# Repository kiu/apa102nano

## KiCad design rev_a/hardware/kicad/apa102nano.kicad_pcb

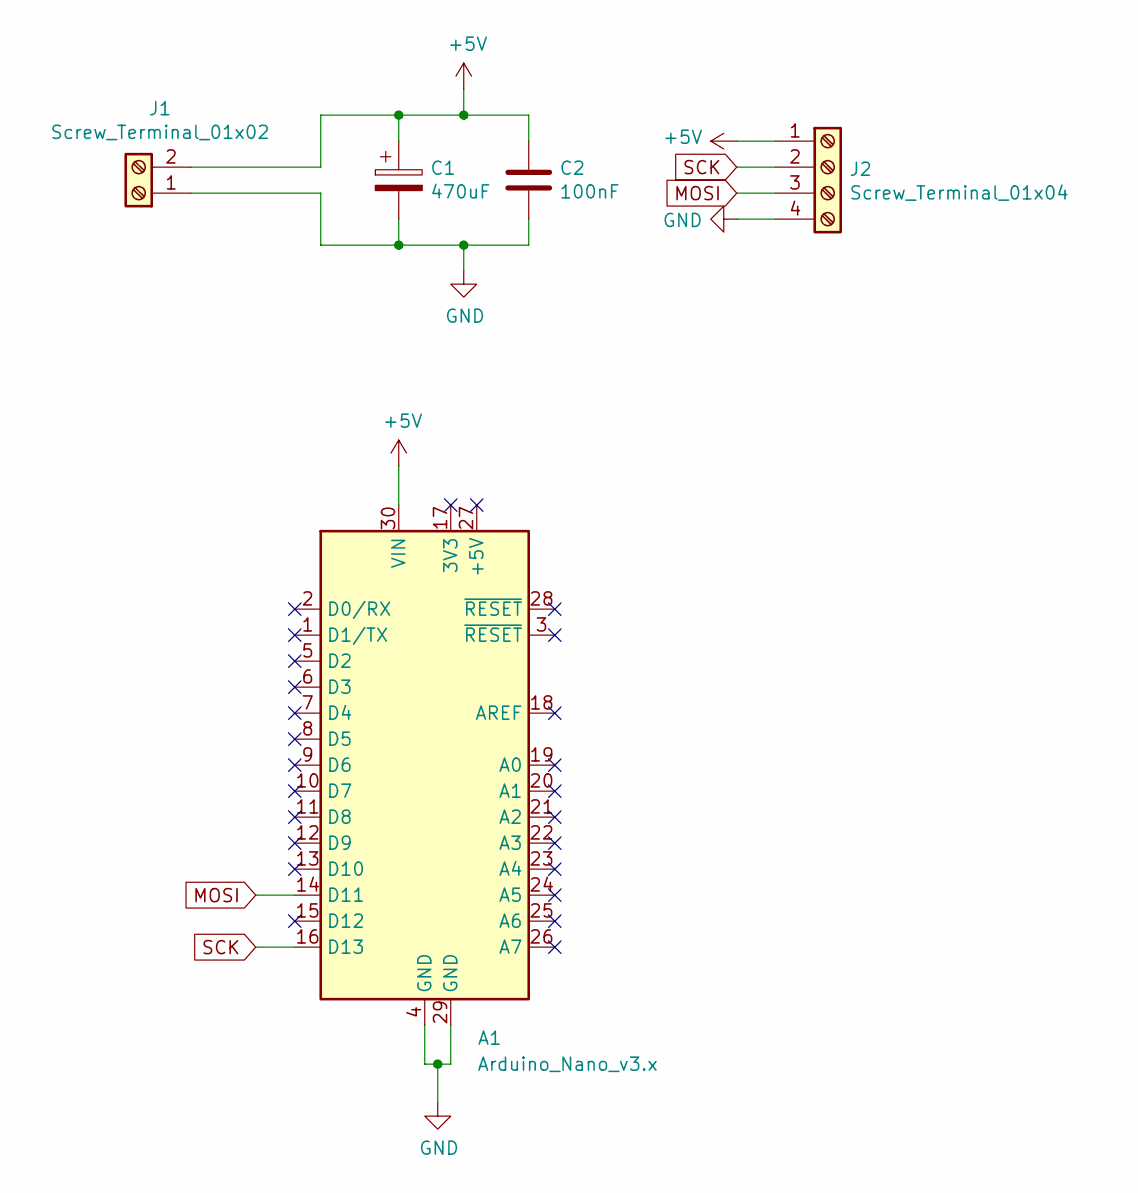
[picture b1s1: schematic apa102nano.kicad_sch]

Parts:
A1: Arduino_Nano_v3.x; Arduino_Nano
C1: 470uF; CP_Tantalum_Case-D_EIA-7343-31_Hand
C2: 100nF; C_0805_HandSoldering
J1: Screw_Terminal_01x02; TerminalBlock_bornier-2_P5.08mm
J2: Screw_Terminal_01x04; TerminalBlock_bornier-4_P5.08mm

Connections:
+5V: A1.30 (VIN), C1.1, C2.1, J1.2, J2.1
GND: A1.4 (GND), A1.29 (GND), C1.2, C2.2, J1.1, J2.4
MOSI: A1.14 (D11), J2.3
SCK: A1.16 (D13), J2.2

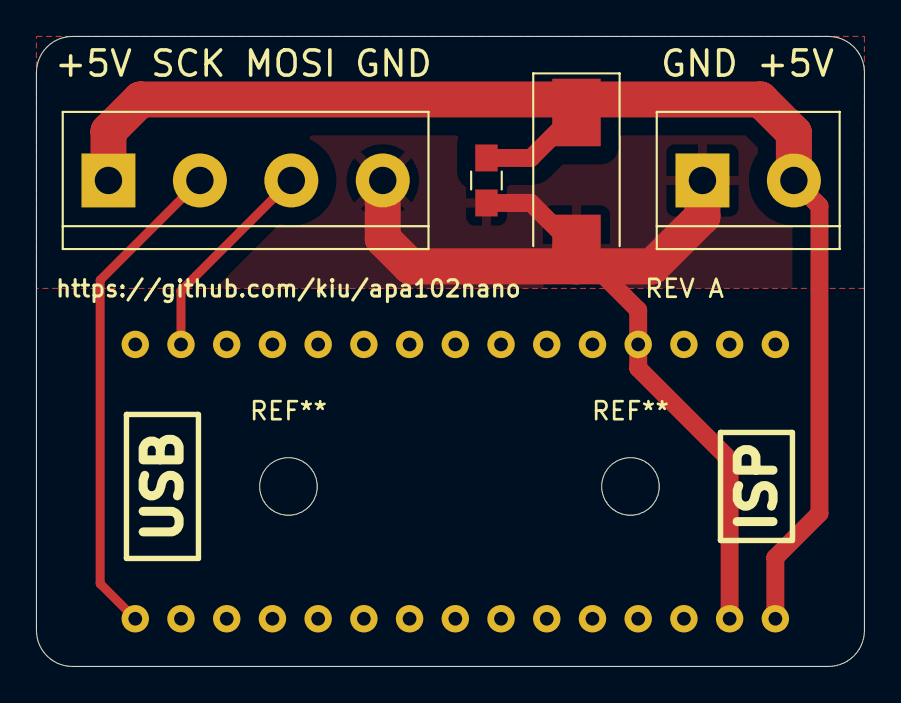
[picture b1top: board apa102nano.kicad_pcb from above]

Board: 2 copper layers, 46.0 x 35.0 mm, 5 parts (0 on the bottom side), 4 nets.

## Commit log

2022-04-24 Tadaaa.
